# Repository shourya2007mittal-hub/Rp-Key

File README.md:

# Rp-Key

SO I wanted to make something like YubiKey but to Enter passwords onto your online accounts or offline password ( like laptop passwords / security passwords) and the most important thing that I focused was that you could enter a password in public without anyone watching it . This add extra privacy to your workflow . So the main focus of my design was to make it small . SO I used RP2350A as micro-controller because it doesn't need an external oscillator hence it saves space on the board . Also there are 4 switches . So you could enter upto 4 different passwords as per your need . There is a boot pin also so that you could update the board as per your need .  The Design is compatible with USB-A and it plugs in perfectly onto it with all the connectors pins aligned . other then that the board has a 3.3V voltage regulator for the MCU and a LED. 

## Why This

It is a simple and is compile too that can be directly plugged on Laptop to enter a password also no one would see you entering the password so it's even better. 

## Features

- Based on RP-2035A Chip
- Has MCP1700x-330xxTT as Voltage Regulator
- has 4 button to enter 4 different password
- had a boot pin as well to update password
- Plugs directly onto type A female

# Project Bill of Materials (BOM) & Cost Summary

## 📦 Components List

| Comment / Part | Quantity | Total Price ($) | Part Link |
| :--- | :---: | :---: | :--- |
| **4.7u** | 6 | $0.1368 | [JLCPCB Link](https://jlcpcb.com/partdetail/24469-CL05A475MP5NRNC/C23733) |
| **100n** | 4 | $0.0216 | [JLCPCB Link](https://jlcpcb.com/partdetail/1877-CL05B104KO5NNNC/C1525) |
| **10uF** | 4 | $0.1548 | [JLCPCB Link](https://jlcpcb.com/partdetail/20411-CL10A106KP8NNNC/C19702) |
| **15p** | 4 | $0.0188 | [JLCPCB Link](https://jlcpcb.com/partdetail/1900-0402CG150J500NT/C1548) |
| **3.3u** | 2 | $1.6456 | [JLCPCB Link](https://jlcpcb.com/partdetail/KOHERelec-MDA40203R3M/C2847470) |
| **1k** | 4 | $0.0320 | [JLCPCB Link](https://jlcpcb.com/partdetail/12256-0402WGF1001TCE/C11702) |
| **10k** | 2 | $0.0132 | [JLCPCB Link](https://jlcpcb.com/partdetail/26274-0402WGJ0103TCE/C25531) |
| **27 ohm** | 4 | $0.0362 | [JLCPCB Link](https://jlcpcb.com/partdetail/25843-0402WGF270JTCE/C25100) |
| **33** | 2 | $0.0068 | [JLCPCB Link](https://jlcpcb.com/partdetail/25848-0402WGF330JTCE/C25105) |
| **1K** | 2 | $0.0120 | [JLCPCB Link](https://jlcpcb.com/partdetail/21904-0603WAF1001T5E/C21190) |
| **SW_Push** | 10 | $3.7180 | [JLCPCB Link](https://jlcpcb.com/partdetail/Korean_HropartsElec-K5_1672SN01/C502360) |
| **RP2350A** | 2 | $3.3980 | [JLCPCB Link](https://jlcpcb.com/partdetail/RaspberryPi-RP2350A/C42411118) |
| **MCP1700x-330xxTT** | 2 | $1.0314 | [JLCPCB Link](https://jlcpcb.com/partdetail/MicrochipTech-MCP1700_3002ETO/C185558) |
| **ABM8-272-T3** | 5 | $1.4705 | [JLCPCB Link](https://jlcpcb.com/partdetail/AbraconLLC-ABM8_272T3/C20625731) |
| **USB_A_PCB_Edge_receptacle** | - | - | - |

---

## 💰 Charge Details & Manufacturing Breakdown

### 🛠️ PCB Fabrication & Assembly Fees
| Item / Description | Price ($) |
| :--- | :---: |
| **PCB Base Price** | $2.00 |
| **Via Covering** | $0.00 |
| **Special Offer** | $2.00 |
| **Setup Fee** | $8.18 |
| **Stencil** | $1.53 |
| **Panel** | $0.00 |
| **Large Size** | $0.00 |
| **Components (12 items)** | $11.65 |
| **Extended components fee** | $12.28 |
| **SMT Assembly** | $0.38 |
| **Hand-soldering labor fee** | $3.58 |
| **Manual Assembly** | $0.10 |
| **Nitrogen reflow soldering** | $0.85 |

### 💵 Cost Totals Summary
| Category | Total Price ($) |
| :--- | :---: |
| **PCB Price Total** | **$2.00** |
| **PCB Shipping** | **$9.68** |
| **Economic PCBA Price Total** | **$48.23** |
| **Grand Total** | **$50.23** |

### Schematic 
<br>

<br>

### PCB Design

### 3D Design

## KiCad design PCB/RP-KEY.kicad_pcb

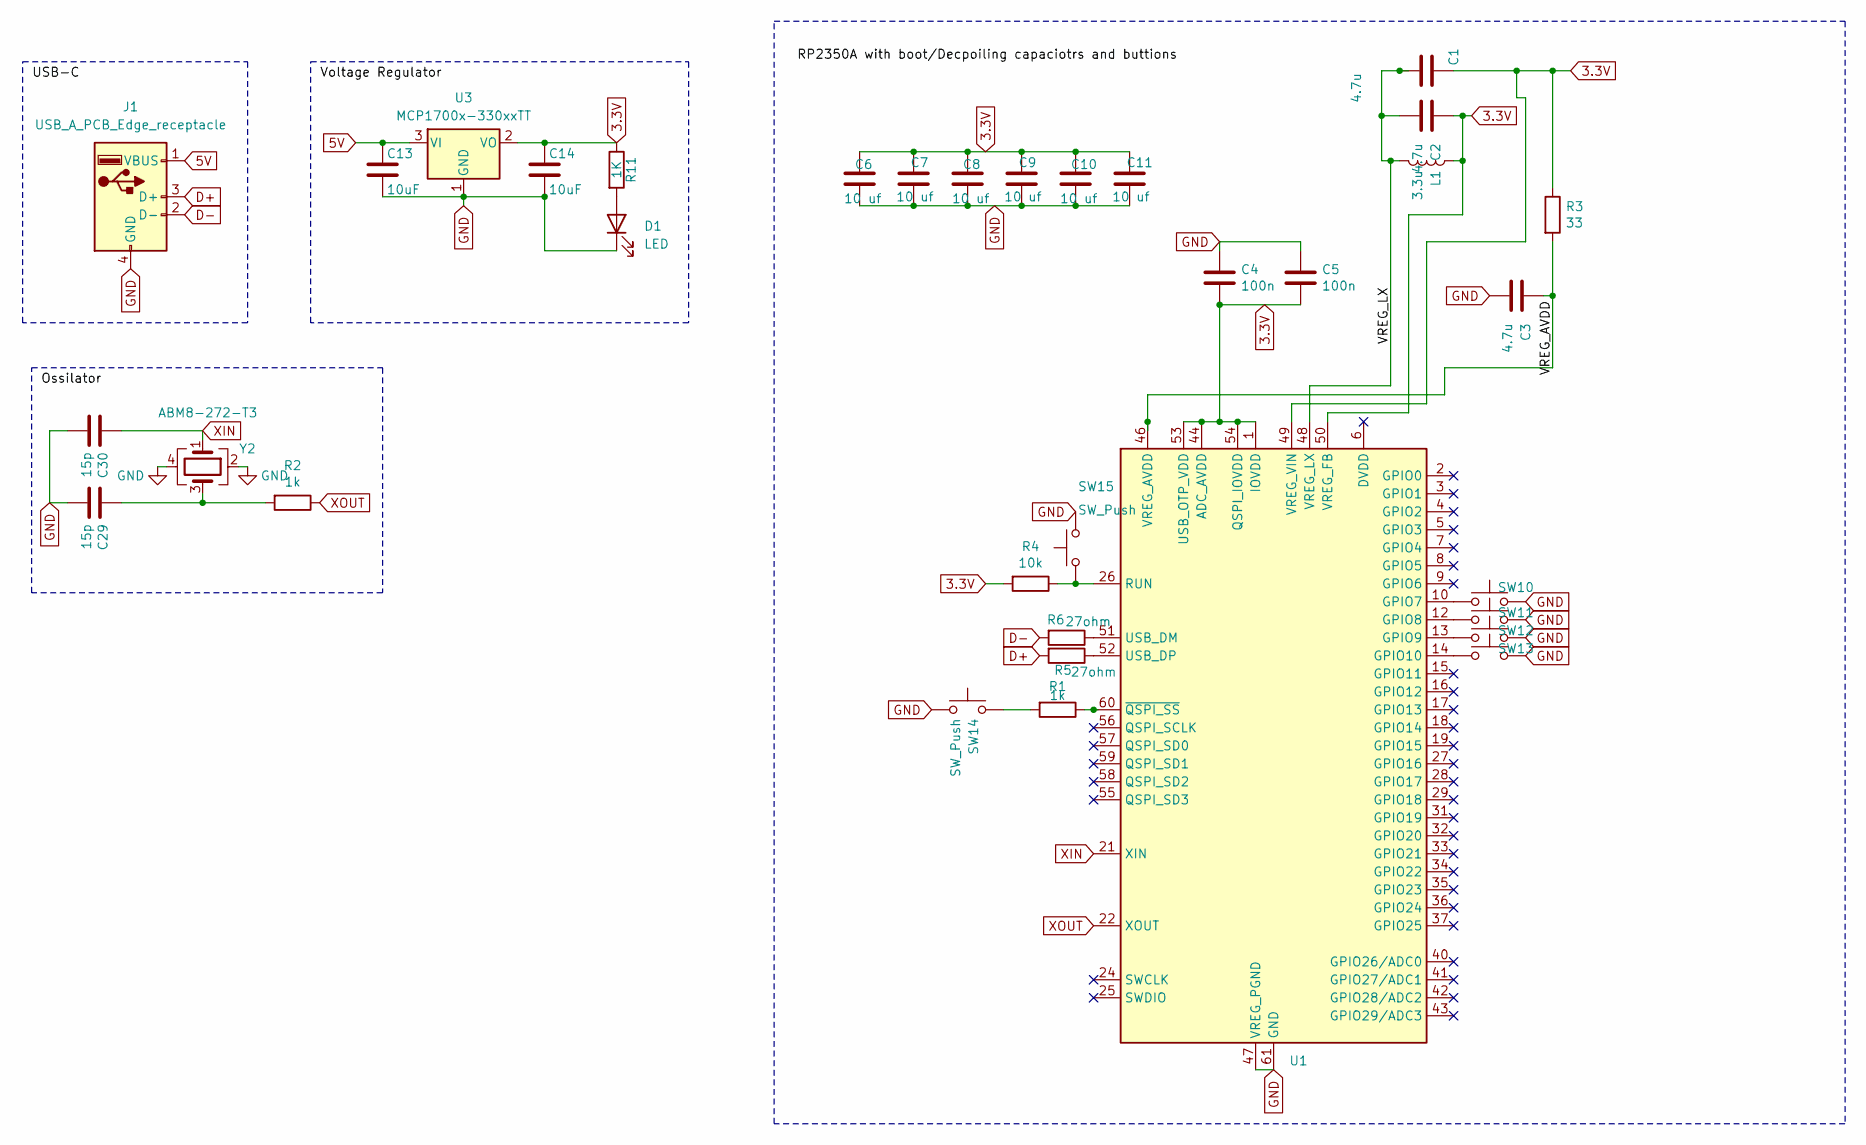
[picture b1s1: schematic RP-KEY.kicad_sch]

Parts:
C1, C2, C3: 4.7u; C_0402_1005Metric
C4, C5: 100n; C_0402_1005Metric
C6, C7, C8, C9, C10, C11: 10 uf; C_0402_1005Metric
C13, C14: 10uF; C_0603_1608Metric
C29, C30: 15p; C_0402_1005Metric
D1: LED; LED_0201_0603Metric
J1: USB_A_PCB_Edge_receptacle
L1: 3.3u; L_0402_1005Metric_Pad0.77x0.64mm_HandSolder
R1, R2: 1k; R_0402_1005Metric
R3: 33; R_0402_1005Metric
R4: 10k; R_0402_1005Metric
R5, R6: 27ohm; R_0402_1005Metric
R11: 1K; R_0603_1608Metric
SW10, SW11, SW12, SW13, SW14, SW15: SW_Push; SW_Tactile_SPST_NO_Straight_CK_PTS636Sx25SMTRLFS
U1: RP2350A; QFN-60-1EP_7x7mm_P0.4mm_EP3.4x3.4mm
U3: MCP1700x-330xxTT; SOT-23
Y2: ABM8-272-T3; Crystal_SMD_3225-4Pin_3.2x2.5mm

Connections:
3.3V: C1.1, C2.1, C4.2, C5.2, C6.1, C7.1, C8.1, C9.1, C10.1, C11.1, C14.1, L1.1, R3.1, R4.2, R11.1, U1.1 (IOVDD), U1.11 (IOVDD), U1.20 (IOVDD), U1.30 (IOVDD), U1.38 (IOVDD), U1.44 (ADC_AVDD), U1.45 (IOVDD), U1.49 (VREG_VIN), U1.50 (VREG_FB), U1.53 (USB_OTP_VDD), U1.54 (QSPI_IOVDD), U3.2 (VO)
5V: C13.1, J1.1 (VBUS), U3.3 (VI)
/VREG_AVDD: C3.1, R3.2, U1.46 (VREG_AVDD)
/VREG_LX: C1.2, C2.2, L1.2, U1.48 (VREG_LX)
D+: J1.3 (D+), R5.2
D-: J1.2 (D-), R6.2
GND: C3.2, C4.1, C5.1, C6.2, C7.2, C8.2, C9.2, C10.2, C11.2, C13.2, C14.2, C29.2, C30.2, D1.1 (K), J1.4 (GND), SW10.2, SW11.2, SW12.2, SW13.2, SW14.1, SW15.2, U1.47 (VREG_PGND), U1.61 (GND), U3.1 (GND), Y2.2, Y2.4
unnamed: C29.1, R2.2, Y2.3
unnamed: D1.2 (A), R11.2
unnamed: R1.2, SW14.2
unnamed: SW10.1, U1.10 (GPIO7)
unnamed: SW11.1, U1.12 (GPIO8)
unnamed: SW12.1, U1.13 (GPIO9)
unnamed: SW13.1, U1.14 (GPIO10)
unnamed: R4.1, SW15.1, U1.26 (RUN)
unnamed: R6.1, U1.51 (USB_DM)
unnamed: R5.1, U1.52 (USB_DP)
unnamed: R1.1, U1.60 (~QSPI_SS)
XIN: C30.1, U1.21 (XIN), Y2.1
XOUT: R2.1, U1.22 (XOUT)

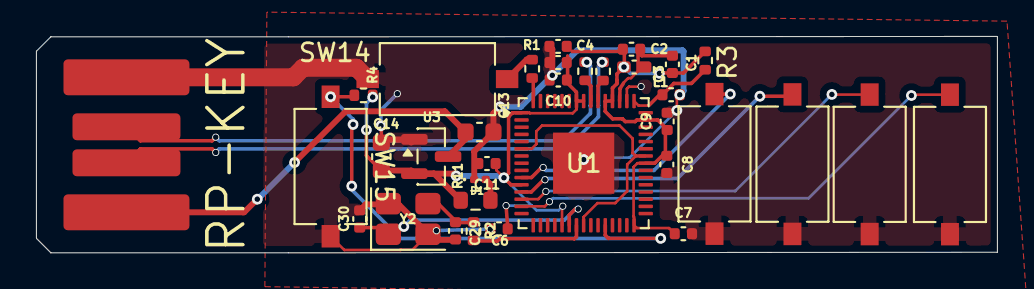
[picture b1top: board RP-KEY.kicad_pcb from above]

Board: 2 copper layers, 53.4 x 12.0 mm, 34 parts (0 on the bottom side), 20 nets.

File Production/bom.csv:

Designator,Footprint,Quantity,Value,LCSC Part #
"C1, C2, C3",0402,3,4.7u,
"C13, C14",0603,2,10uF,
"C29, C30",0402,2,15p,
"C4, C5",0402,2,100n,
D1,0201,1,LED,
J1,USB_A_PCB_Edge_receptacle,1,USB_A_PCB_Edge_receptacle,
L1,0402,1,3.3u,
"R1, R2",0402,2,1k,
R11,0603,1,1K,
R3,0402,1,33,
"R5 ,R6 ",0402,2,27 ohm, 
" SW13, SW14",SW_Tactile_SPST_NO_Straight_CK_PTS636Sx25SMTRLFS,2,SW_Push,
U1,QFN-60-1EP_7x7mm_P0.4mm_EP3.4x3.4mm,1,RP2350A,
U3,SOT-23,1,MCP1700x-330xxTT,
Y2,Crystal_SMD_3225-4Pin_3.2x2.5mm,1,ABM8-272-T3,
